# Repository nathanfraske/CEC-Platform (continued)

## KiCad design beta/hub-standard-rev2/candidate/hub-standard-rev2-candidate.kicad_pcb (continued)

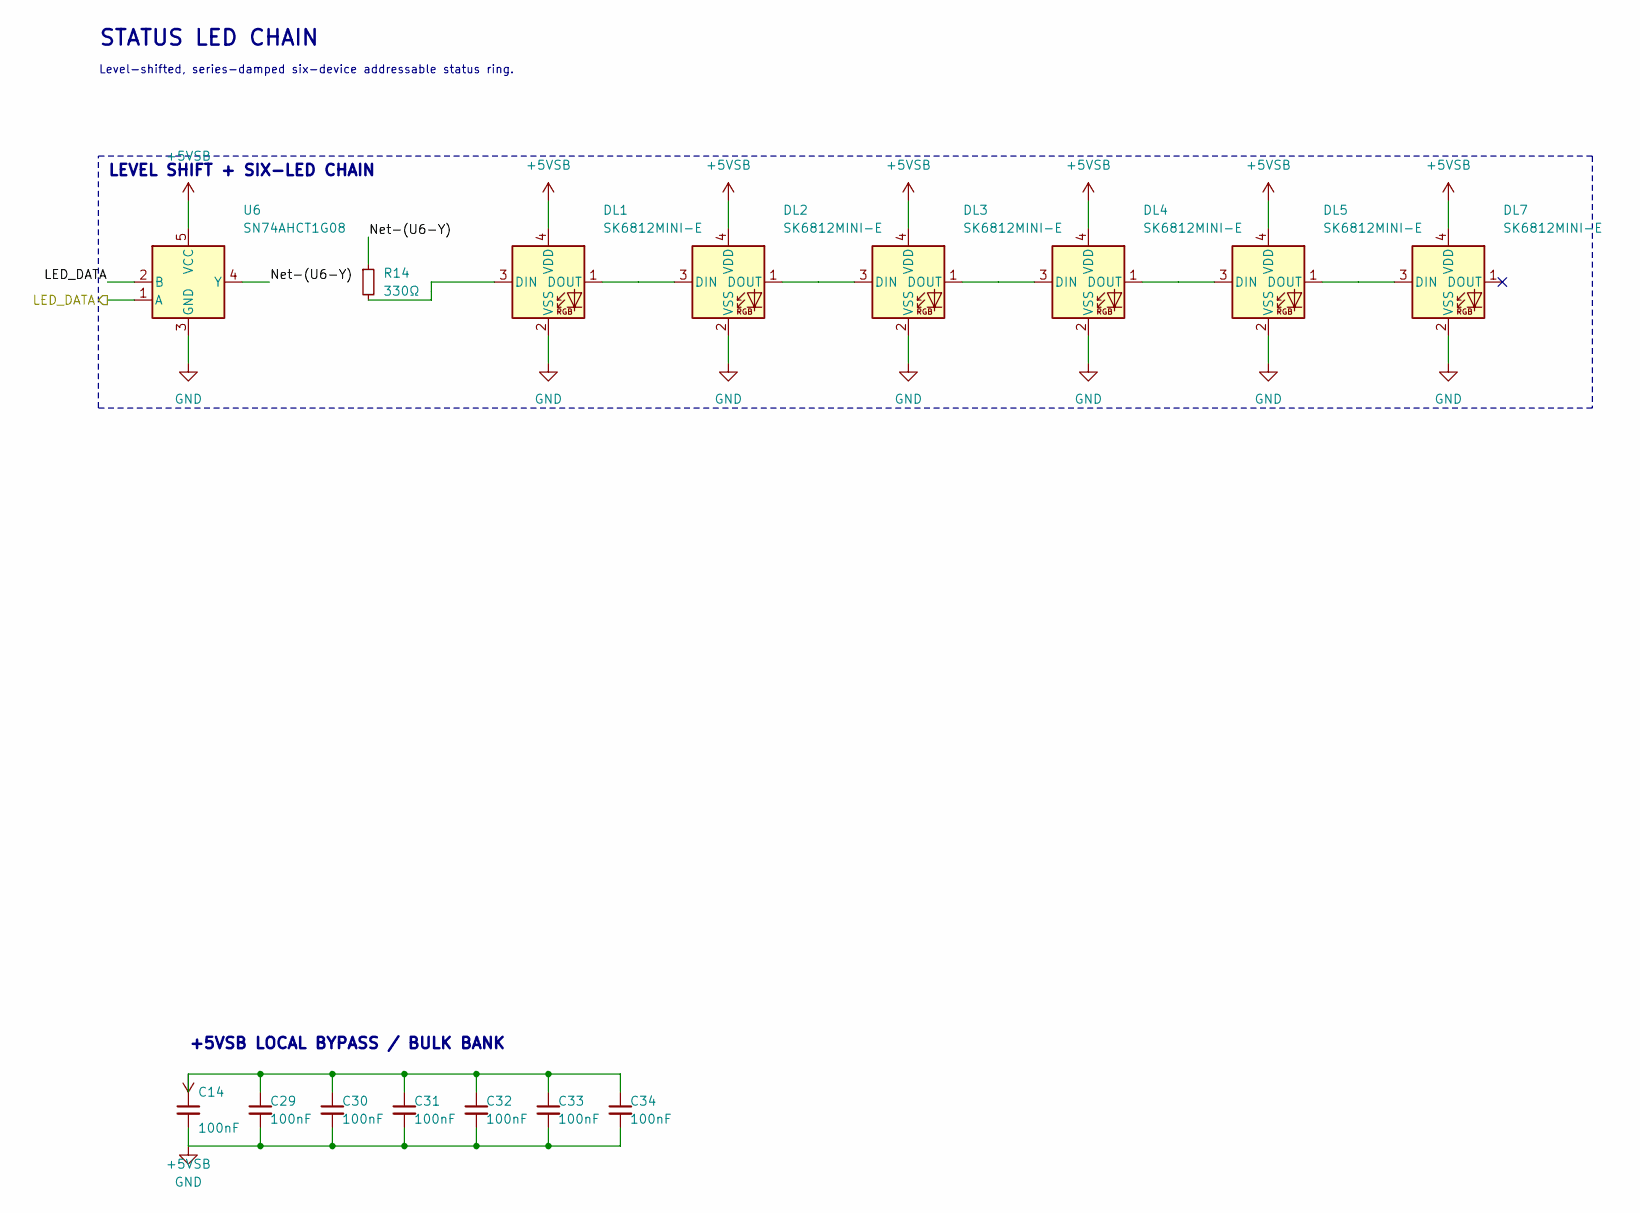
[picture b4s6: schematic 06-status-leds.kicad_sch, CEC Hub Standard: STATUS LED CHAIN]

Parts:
C14, C29, C30, C31, C32, C33, C34: 100nF; C_0402_1005Metric; MPN CL05B104KO5NNNC; LCSC C1525
DL1, DL2, DL3, DL4, DL5, DL7: SK6812MINI-E; LED_SK6812MINI-E_3.2x2.8mm_P1.5mm_ReverseMount; MPN SK6812MINI-E; LCSC C5149201
R14: 330Ω; R_0402_1005Metric; MPN 0402WGF3300TCE; LCSC C25104
U6: SN74AHCT1G08; SOT-23-5; MPN SN74AHCT1G08DBVR; LCSC C113521

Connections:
+5VSB: C14.1, C29.1, C30.1, C31.1, C32.1, C33.1, C34.1, DL1.4 (VDD), DL2.4 (VDD), DL3.4 (VDD), DL4.4 (VDD), DL5.4 (VDD), DL7.4 (VDD), U6.5 (VCC); also elsewhere on the board
/LED_DATA: U6.1 (A), U6.2 (B); also elsewhere on the board
/STATUS LED CHAIN/Net-(U6-Y): R14.1, U6.4 (Y)
unnamed: DL1.3 (DIN), R14.2
unnamed: DL1.1 (DOUT), DL2.3 (DIN)
unnamed: DL2.1 (DOUT), DL3.3 (DIN)
unnamed: DL3.1 (DOUT), DL4.3 (DIN)
unnamed: DL4.1 (DOUT), DL5.3 (DIN)
unnamed: DL5.1 (DOUT), DL7.3 (DIN)

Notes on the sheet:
STATUS LED CHAIN
Level-shifted, series-damped six-device addressable status ring.
+5VSB LOCAL BYPASS / BULK BANK
LEVEL SHIFT + SIX-LED CHAIN

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
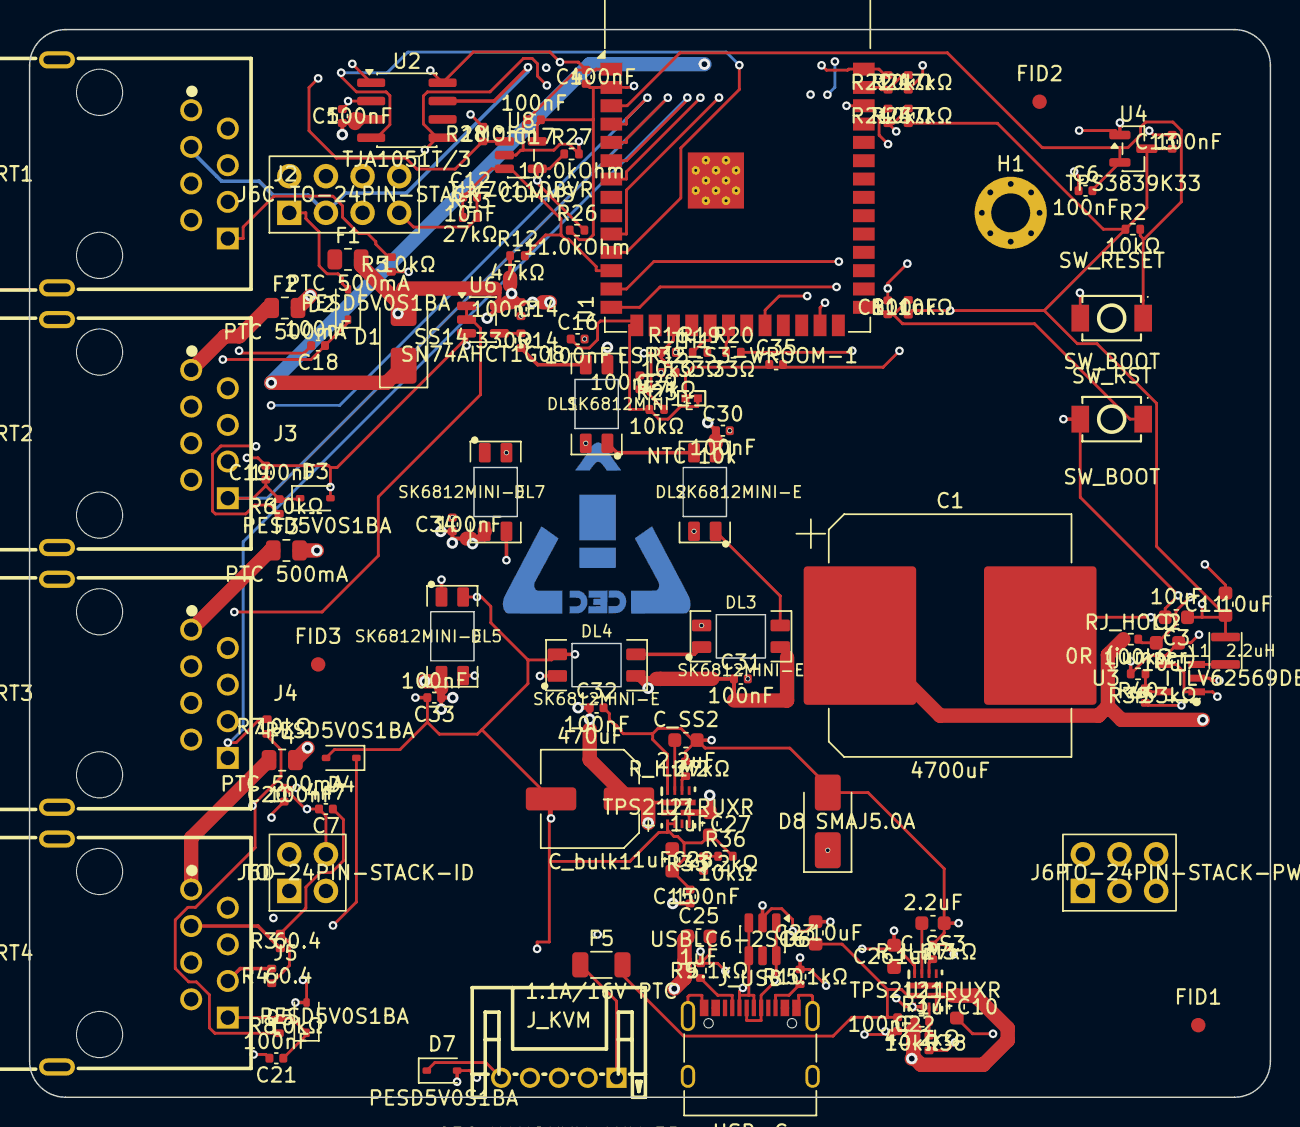
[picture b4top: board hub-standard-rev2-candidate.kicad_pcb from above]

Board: 6 copper layers, 86.0 x 74.0 mm, 115 parts (1 on the bottom side), 58 nets.

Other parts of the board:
FID1, FID2, FID3: Fiducial_1mm_Mask2mm
H1: MountingHole_2.7mm_M2.5_Pad_Via
LOGO1: CEC_Logo_Copper

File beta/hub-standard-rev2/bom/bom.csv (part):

Reference,Qty,Value,Footprint,MPN,Manufacturer,LCSC,LC_Stock,Chosen_Distributor,Datasheet,Validated,DNP,Notes
"C1,C37",2,4700uF,CP_Elec_Lelon_VZH_18x16.5,VZH472M1CTR-1816,Lelon,C249940,,,https://www.lelon.com.tw/upload/guides/2026%20Capacitor%20Ca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,,,"Parallel isolated reservoir; 9400uF nominal bank, 5264uF at initial -20% and endurance -30%. Each 16V, D18x16.5mm (17mm max), 5000h at 105C. OQ-56 bench qualification pending."
C12,1,10nF,C_0402_1005Metric,CL05B103KB5NNNC,Samsung,C15195,,,https://product.samsungsem.com/mlcc/CL05B103KB5NNN.do,,,
"C2,C3,C23",3,10uF,C_0603_1608Metric,CL10A106MA8NRNC,Samsung,C96446,,,https://product.samsungsem.com/mlcc/CL10A106MA8NRN.do,,,U11 IN2 (KVM 5V) bulk -- the hub's own 0603 10uF line.
C11,1,22uF,C_0603_1608Metric,CL10A226MP8NUNE,Samsung,C86295,,,https://product.samsungsem.com/mlcc/CL10A226MP8NUN.do,,,ESP32-S3-WROOM-1 U1 local 22uF 10V X5R VDD33 bulk capacitor; compact 0603 package permits a complete pin-2 bulk plus C36 high-frequency bypass cell.
"C4,C5,C6,C8,C13,C14,C15,C16,C17,C18,C19,C20,C21,C22,C29,C30,C31,C32,C33,C34,C35,C36",22,100nF,C_0402_1005Metric,CL05B104KO5NNNC,Samsung,C1525,,,https://product.samsungsem.com/mlcc/CL05B104KO5NNN.do,,,"DETECT immunity filter (owner VRM-coupling concern 2026-07-15): 100n on the 10k-source analog identity line; ~1ms settle, irrelevant to detection; kills near-field pickup.,Dedicated 100nF EMC bypass from TJA1051T/3 VIO pin 5 to VCC pin 3; place directly across both pins.,Dedicated 100nF local bypass for DL2; place directly at VDD/VSS.,Dedicated 100nF local bypass for DL3; place directly at VDD/VSS.,Dedicated 100nF local bypass for DL4; place directly at VDD/VSS.,Dedicated 100nF local bypass for DL5; place directly at VDD/VSS.,Dedicated 100nF local bypass for DL7; place directly at VDD/VSS.,SN74AHCT1G08 U6 local 100nF bypass; place directly at VCC/GND.,U11 IN2 (KVM 5V) bypass.,ESP32-S3-WROOM-1 U1 local VDD33 high-frequency bypass; place directly at U1 pin 2 with an immediate ground return."
C7,1,4n7,C_0402_1005Metric,0402B472K500NT,Fenghua,C1538,,,,,,
"C10,C25,C26,C27,C28",5,1uF,C_0603_1608Metric,CL10A105KB8NNNC,Samsung,C15849,,,https://product.samsungsem.com/mlcc/CL10A105KB8NNN.do,,,"U11 USB_VBUS input and output local bypass; U7 +5V_SYS primary input and PSU_5V_KVM backup input local bypass. Dedicated low-ESR X5R ceramics; place directly at the TPS2121 pins."
"C_SS2,C_SS3",2,2.2uF,C_0603_1608Metric,CL10A225KO8NNNC,Samsung,C23630,,,,,,"U11/U7 2.2uF soft-start; TI Table 9-1 typical interpolation gives about 40V/s (125ms to 5V), not 10ms. Effective capacitance and cold/hot startup require bench confirmation."
C_bulk1,1,470uF,CP_Elec_6.3x7.7,RVT1A471M0607,Lelon,C335982,,,,,,Bulk surge cap on Hub +5VSB distribution
D1,1,SS14,D_SMA,SS14,MDD (Microdiode Semiconductor),C2480,,,https://www.lcsc.com/datasheet/C2480.pdf,,,"MDD SS14 40V 1A Schottky hold-up isolation diode; cathode pin 1 to +5V_HOLD, anode pin 2 to the selected +5VSB source. Maximum specified VF is 0.55V at 1A."
"D2,D3,D4,D5,D7",5,PESD5V0S1BA,D_SOD-323,PESD5V0S1BA,HXY MOSFET,C5261083,,,https://www.lcsc.com/datasheet/C5261083.pdf,,,"Low-cap DETECT ESD diode (pin8 hot-plug, spec 2.4 v2.0)"
D6,1,USBLC6-2SC6,SOT-23-6,USBLC6-2SC6,UMW,C2687116,,,https://datasheet.lcsc.com/lcsc/2206231215_UMW-Youtai-Semico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,,,
D8,1,SMAJ5.0A,D_SMA,SMAJ5.0A,MDD (Microdiode Semiconductor),C113952,,,https://www.lcsc.com/datasheet/C113952.pdf,,,"Stack-power TVS at J6P +5V_SYS; 5V working, clamps line transients at the board-to-board entry."
"DL1,DL2,DL3,DL4,DL5,DL7",6,SK6812MINI-E,LED_SK6812MINI-E_3.2x2.8mm_P1.5mm_ReverseMount,SK6812MINI-E,OPSCO Optoelectronics,C5149201,,,https://datasheet.lcsc.com/lcsc/1810231311_OPSCO-Optoelectro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,,,
"F1,F2,F3,F4",4,PTC 500mA,R_0805_2012Metric,SMD0805-050-6,generic (JLC catalog),C46640983,,,,,,"Per-port RJ45-VCC polyfuse (owner ruling 2026-07-15): fault isolation -- a shorted patch cable or failed module trips ONE port instead of browning out the shared 5VSB system (the TPS2121 limit is total, not per-port). 0805 PTC, 500mA hold, 6V rated. ~150mV drop at load absorbed by module LDO headroom."
F5,1,1.1A/16V PTC,R_1206_3216Metric,FSMD110-16-1206R,FUZETEC,C5707763,,,,,,"1.1A hold/2.2A trip/16V resettable PTC polyfuse, KVM 5V ingress defense layer 2 (spec Sec 2.9 v1.6.0). F1-F4 are the 2026-07-15 per-port 500mA PTCs -- unrelated position."
J2,1,PORT1,RJ45_FTP_Shielded_Horizontal,KH-RJ45-58-8P8C,Kinghelm,C2683360,,,https://www.lcsc.com/datasheet/C2683360.pdf,,,
J3,1,PORT2,RJ45_FTP_Shielded_Horizontal,KH-RJ45-58-8P8C,Kinghelm,C2683360,,,https://www.lcsc.com/datasheet/C2683360.pdf,,,
J4,1,PORT3,RJ45_FTP_Shielded_Horizontal,KH-RJ45-58-8P8C,Kinghelm,C2683360,,,https://www.lcsc.com/datasheet/C2683360.pdf,,,
J5,1,PORT4,RJ45_FTP_Shielded_Horizontal,KH-RJ45-58-8P8C,Kinghelm,C2683360,,,https://www.lcsc.com/datasheet/C2683360.pdf,,,
J6C,1,TO-24PIN-STACK-COMMS,PinSocket_2x04_P2.54mm_Vertical,SSQ-104-01-G-D,Samtec,,,,https://suddendocs.samtec.com/catalog_english/ssw_th.pdf,,,Exact 2x4 Hub socket; mates ATX TSW-104-17-G-D in the provisional 22mm dead-bug stack; hardware and assembly qualification pending. STREAM_P/N are intentionally NC on both Standard boards.
J6D,1,TO-24PIN-STACK-ID,PinSocket_2x02_P2.54mm_Vertical,SSQ-102-01-G-D,Samtec,,,,https://suddendocs.samtec.com/catalog_english/ssw_th.pdf,,,Exact 2x2 Hub socket; mates ATX TSW-102-17-G-D in the provisional 22mm dead-bug stack; hardware and assembly qualification pending. RSVD is intentionally NC.
J6P,1,TO-24PIN-STACK-PWR,PinSocket_2x03_P2.54mm_Vertical,SSQ-103-01-G-D,Samtec,,,,https://suddendocs.samtec.com/catalog_english/ssw_th.pdf,,,Exact 2x3 Hub socket; mates ATX TSW-103-17-G-D in the provisional 22mm dead-bug stack; hardware and assembly qualification pending.
J_KVM?,1,CEC_NANOKVM_AUX_5P,JST_PH_S5B-PH-K-S_1x05_P2.00mm_Horizontal,S5B-PH-K-S(LF)(SN),JST,C157923,,,,,,
J_USB,1,USB-C,USB_C_Receptacle_GCT_USB4215-03-A,USB4215-03-A,GCT,C37616412,,,https://mm.digikey.com/Volume0/opasdata/d220001/medias/docus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,,,
L1,1,2.2uH,VLS252010HBX-2R2M-1,VLS252010HBX-2R2M-1,TDK,C88527,,,https://product.tdk.com/en/search/inductor/inductor/smd/info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,,,"2.2uH shielded buck inductor, 2.3A Isat max / 1.76A thermal-rated"
"R12,R15,R21,R23",4,47kΩ,R_0402_1005Metric,0402WGF4702TCE,UNI-ROYAL,C25792,,,,,,
"R35,R37",2,43.2kΩ,R_0402_1005Metric,0402WGF4322TCE,UNI-ROYAL,C25894,,,https://www.lcsc.com/product-detail/C25894.html,,,"U11/U7 OV1 divider tops; 43.2k/10k gives 5.639V nominal and 5.287..5.948V static extremes; dynamic margin remains a qualification gate."
"R13,R_ILIM2,R_ILIM3",3,27kΩ,R_0402_1005Metric,0402WGF2702TCE,UNI-ROYAL,C25771,,,,,,"U11 and U7 ILIM straps (~3.8A); F5's 1.1A hold rating remains the tighter NanoKVM-source protection."
R14,1,330Ω,R_0402_1005Metric,0402WGF3300TCE,UNI-ROYAL,C25104,,,,,,
"R19,R20",2,33Ω,R_0402_1005Metric,0402WGF330JTCE,UNI-ROYAL,C25105,,,,,,
"R2,R5,R6,R7,R8,R11,R16,R22,R24,R25,R36,R38",12,10kΩ,R_0402_1005Metric,0402WGF1002TCE,UNI-ROYAL,C25744,,,,,,"Includes U11 and U7 OV1-divider bottom legs; paired with 43.2k top legs for 5.639V nominal cutoff."
R26,1,11.0kOhm,R_0402_1005Metric,RC0402FR-0711KL,YAGEO,C138063,,,https://www.lcsc.com/product-detail/C138063.html,,,"Selected-rail dropout threshold divider, top leg (1%). With R27=10k and R28=1M hysteresis, sets U8 IN- near 1.59V for a nominal 4.36V trip on the upstream +5VSB BLACKOUT_SENSE divider."
R27,1,10.0kOhm,R_0402_1005Metric,0402WGF1002TCE,UNI-ROYAL,C25744,,,,,,"W12 comparator threshold divider, bottom leg (1%)."
R28,1,1MOhm,R_0402_1005Metric,0402WGF1004TCE,UNI-ROYAL,C26083,,,,,,"Selected-rail dropout comparator hysteresis feedback (~1M), OUT -> COMP_THRESH. BLACKOUT_SENSE remains available to the ADC for logging while U8 supplies the hardware interrupt."
"R3,R4",2,60.4,R_0402_1005Metric,GR0402F60R4TAG00,Viking,C49654185,,,,,,
R39,1,453kΩ,R_0402_1005Metric,0402WGF4533TCE,UNI-ROYAL,C27009,,,https://www.lcsc.com/product-detail/C27009.html,,,Hub buck FB top; 3.318V nominal
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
